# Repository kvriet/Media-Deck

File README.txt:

// README for the Media Deck by C.M. van Riet - 6 August 2021

Components:
- Arduino Pro Micro (with or without headers)
- 6x Cherry MX (-like) switches
- 6x Cherry MX compatible keycaps
- 6x diode (1N4148 SOD-323)
- 6x 100nF cap (0805) OPTIONAL
- 6x reverse-mounted LED (SK6812 3228)
- 1x slider potentiometer 35mm 3 foot
- 2x female or male header
- 4x mini screw (M1.7x5)

Printing and assembly:
Print the base without supports (0.2 or 0.3 mm layer height).
Print the top with supports (upside down) and support on build plate only (0.2mm layer height).

For a deck with Arduino hidden: print 'top closed' and solder Arduino onto PCB with male headers. Cut off excess pin length.

For a deck with Arduino visible: print 'top open' and solder female headers onto pcb and male headers onto Arduino. 

Solder PCB as indicated by silkscreen.

Join 3 parts (top, PCB, base) and screw shut.

Software:
Choose your own key codes for the media deck and upload sketch to Arduino Pro Micro (choosing Arduino Leonardo in Arduino application also works).

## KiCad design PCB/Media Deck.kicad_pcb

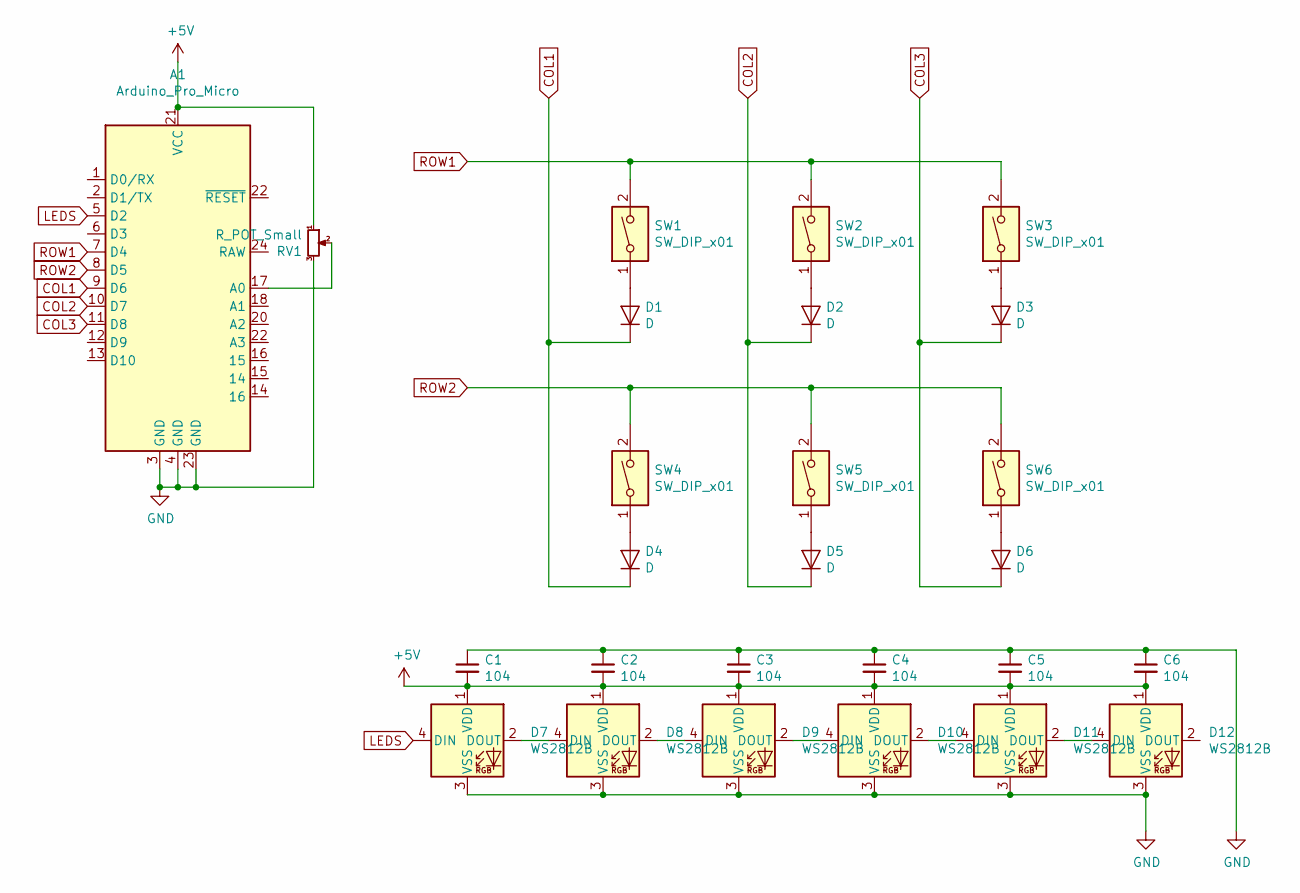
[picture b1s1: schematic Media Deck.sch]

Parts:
A1: Arduino_Pro_Micro
C1, C2, C3, C4, C5, C6: 104; C_0805_2012Metric
D1, D2, D3, D4, D5, D6: D; D_0805_2012Metric_Pad1.15x1.40mm_HandSolder
D7, D8, D9, D10, D11, D12: WS2812B; LED_SK6812MINI_REVERSE
RV1: R_POT_Small; Pot_Slider_35mm
SW1, SW2, SW3, SW4, SW5, SW6: SW_DIP_x01; SW_Cherry_MX_1.00u_Plate

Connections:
+5V: A1.21 (VCC), C1.2, C2.2, C3.2, C4.2, C5.2, C6.2, D7.1 (VDD), D8.1 (VDD), D9.1 (VDD), D10.1 (VDD), D11.1 (VDD), D12.1 (VDD), RV1.1
COL1: A1.9 (D6), D1.1 (K), D4.1 (K)
COL2: A1.10 (D7), D2.1 (K), D5.1 (K)
COL3: A1.11 (D8), D3.1 (K), D6.1 (K)
GND: A1.3 (GND), A1.4 (GND), A1.23 (GND), C1.1, C2.1, C3.1, C4.1, C5.1, C6.1, D7.3 (VSS), D8.3 (VSS), D9.3 (VSS), D10.3 (VSS), D11.3 (VSS), D12.3 (VSS), RV1.3
LEDS: A1.5 (D2), D7.4 (DIN)
unnamed: A1.17 (A0), RV1.2
unnamed: D1.2 (A), SW1.1
unnamed: D2.2 (A), SW2.1
unnamed: D3.2 (A), SW3.1
unnamed: D4.2 (A), SW4.1
unnamed: D5.2 (A), SW5.1
unnamed: D6.2 (A), SW6.1
unnamed: D7.2 (DOUT), D8.4 (DIN)
unnamed: D8.2 (DOUT), D9.4 (DIN)
unnamed: D10.2 (DOUT), D11.4 (DIN)
unnamed: D9.2 (DOUT), D10.4 (DIN)
unnamed: D11.2 (DOUT), D12.4 (DIN)
ROW1: A1.7 (D4), SW1.2, SW2.2, SW3.2
ROW2: A1.8 (D5), SW4.2, SW5.2, SW6.2

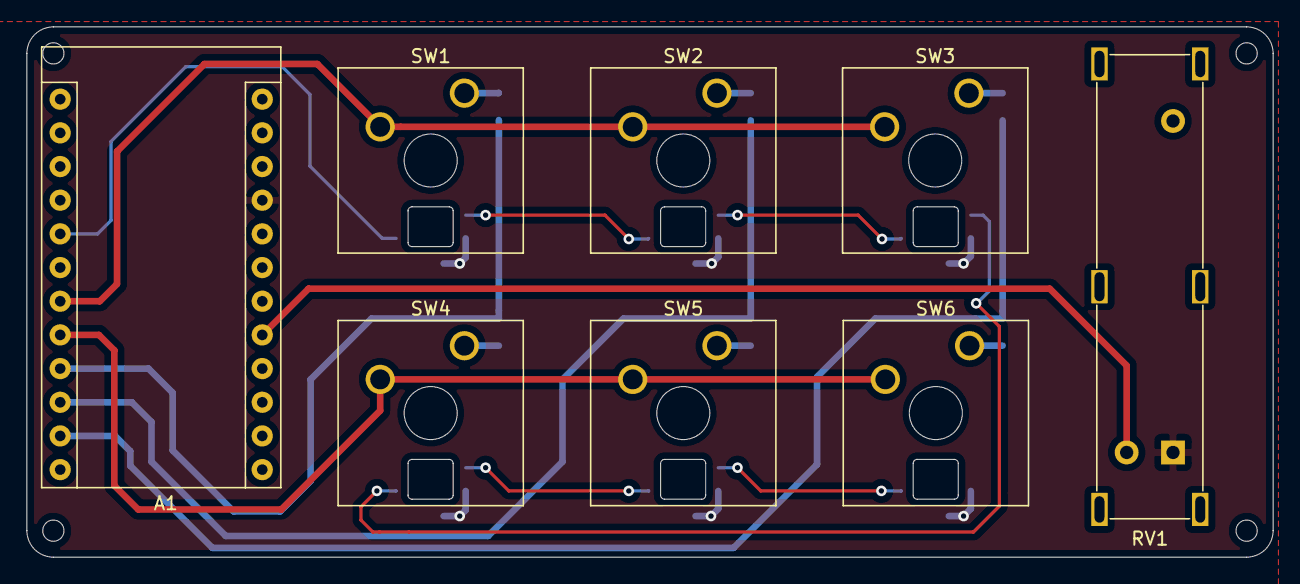
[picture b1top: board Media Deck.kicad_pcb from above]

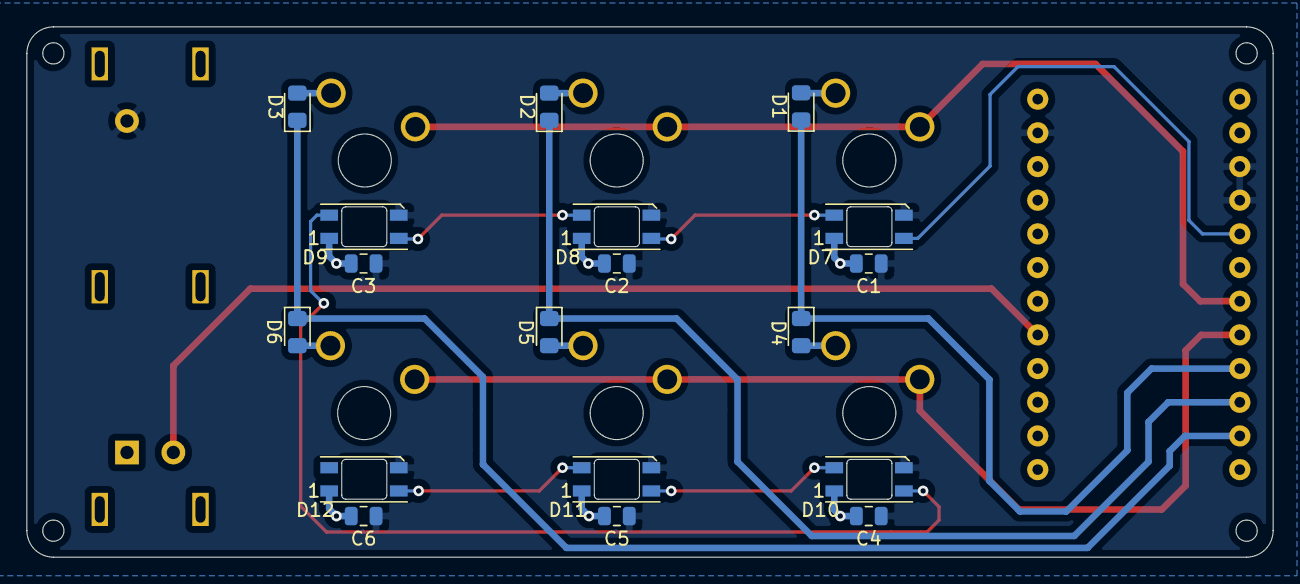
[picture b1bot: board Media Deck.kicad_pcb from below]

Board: 2 copper layers, 94.0 x 40.0 mm, 26 parts (18 on the bottom side), 20 nets.
